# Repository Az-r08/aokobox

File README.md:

# AokoBox: mid profile hitbox-layout fightstick
a modified flatbox that uses mx style switches

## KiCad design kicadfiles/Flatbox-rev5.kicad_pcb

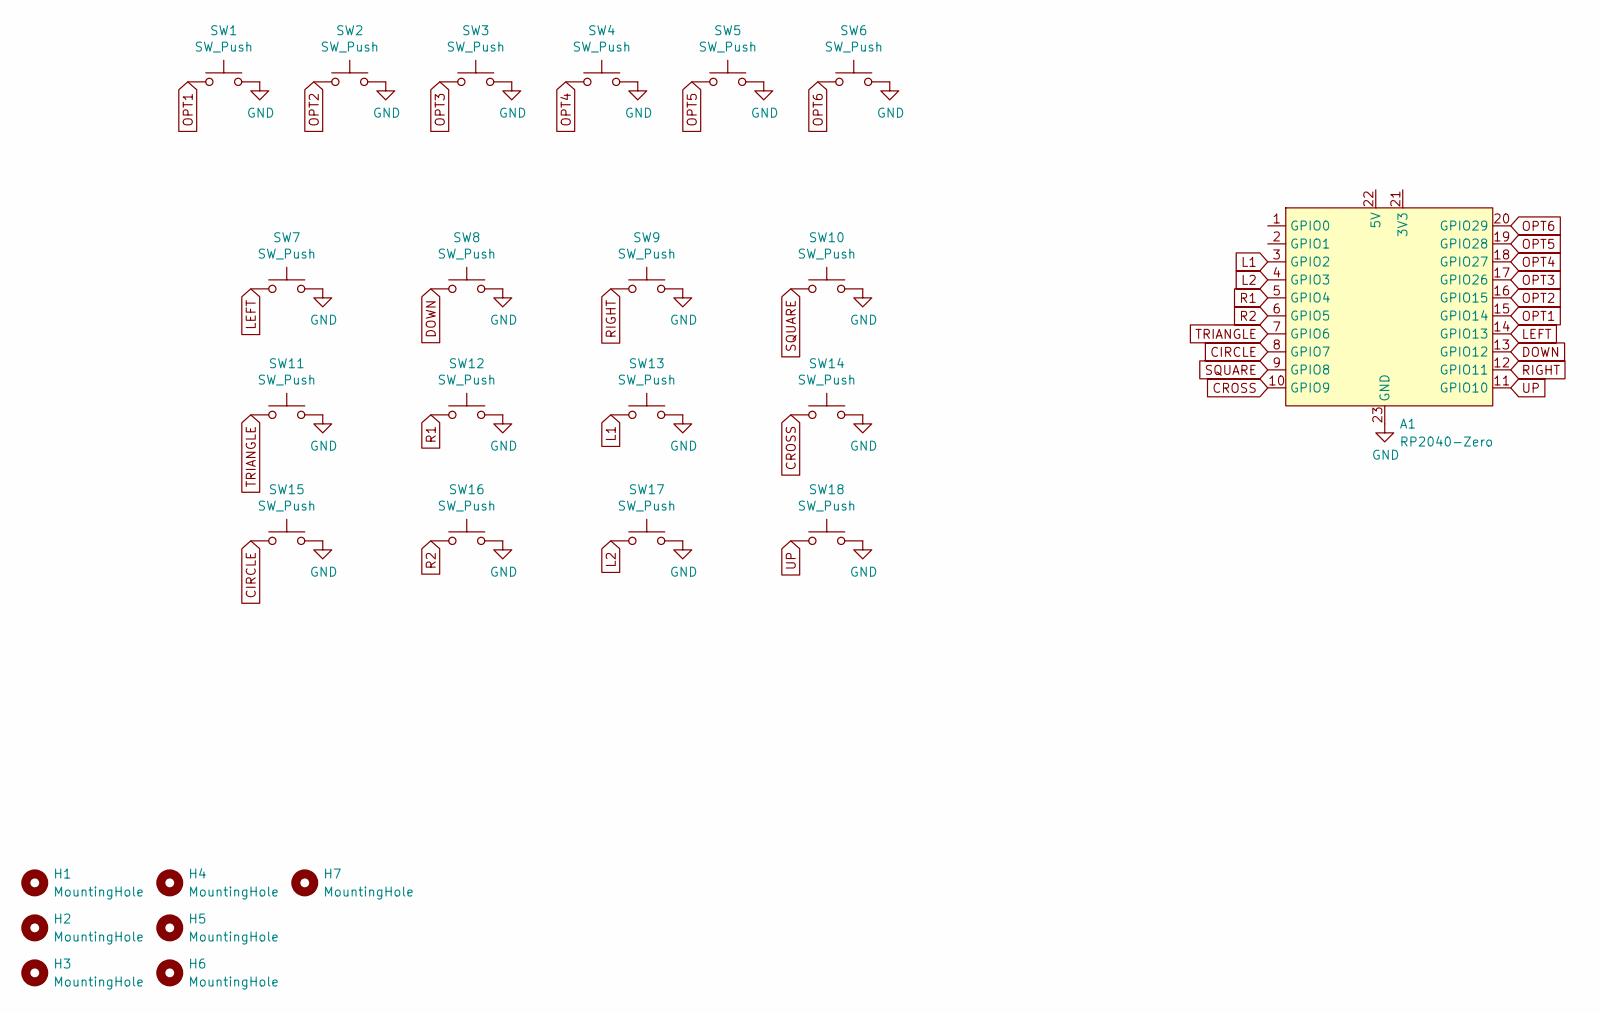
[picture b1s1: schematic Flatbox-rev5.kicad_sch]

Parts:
A1: RP2040-Zero
H1, H2, H3, H4, H5, H6, H7: MountingHole; MountingHole_3.2mm_M3
SW1, SW2, SW3, SW4, SW5, SW6: SW_Push; SW_PUSH_6mm_H5mm
SW7: SW_Push; Kailh_socket_MX_platemount
SW8, SW9, SW10, SW11, SW12, SW13, SW14, SW15, SW16, SW17, SW18: SW_Push; Kailh_socket_MX_optional

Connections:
CIRCLE: A1.8 (GPIO7), SW15.1
CROSS: A1.10 (GPIO9), SW14.1
DOWN: A1.13 (GPIO12), SW8.1
GND: A1.23 (GND), SW1.2, SW2.2, SW3.2, SW4.2, SW5.2, SW6.2, SW7.2, SW8.2, SW9.2, SW10.2, SW11.2, SW12.2, SW13.2, SW14.2, SW15.2, SW16.2, SW17.2, SW18.2
L1: A1.3 (GPIO2), SW13.1
L2: A1.4 (GPIO3), SW17.1
LEFT: A1.14 (GPIO13), SW7.1
OPT1: A1.15 (GPIO14), SW1.1
OPT2: A1.16 (GPIO15), SW2.1
OPT3: A1.17 (GPIO26), SW3.1
OPT4: A1.18 (GPIO27), SW4.1
OPT5: A1.19 (GPIO28), SW5.1
OPT6: A1.20 (GPIO29), SW6.1
R1: A1.5 (GPIO4), SW12.1
R2: A1.6 (GPIO5), SW16.1
RIGHT: A1.12 (GPIO11), SW9.1
SQUARE: A1.9 (GPIO8), SW10.1
TRIANGLE: A1.7 (GPIO6), SW11.1
UP: A1.11 (GPIO10), SW18.1

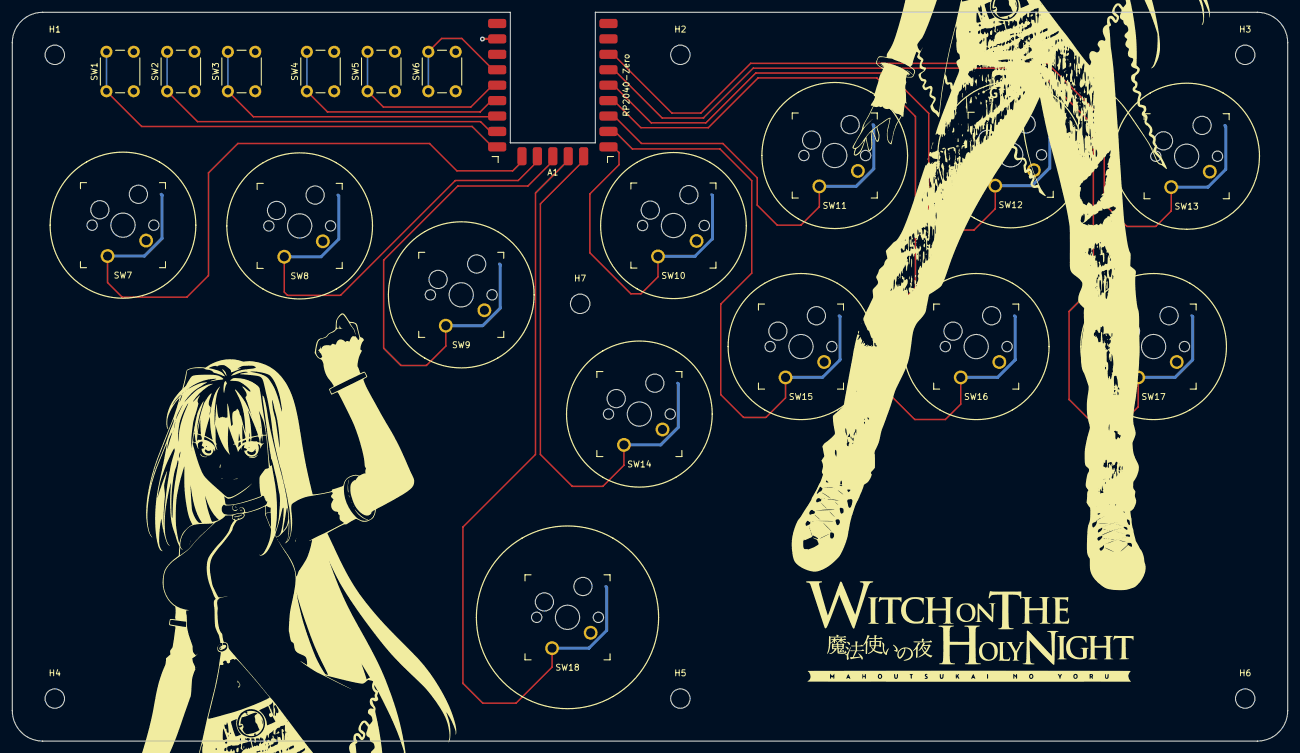
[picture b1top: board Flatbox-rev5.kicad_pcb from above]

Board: 2 copper layers, 210.0 x 120.0 mm, 26 parts (0 on the bottom side), 19 nets.

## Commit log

2023-09-13 kicad files
    havent plotted, only kicad files available
2023-11-22 files
    upload
